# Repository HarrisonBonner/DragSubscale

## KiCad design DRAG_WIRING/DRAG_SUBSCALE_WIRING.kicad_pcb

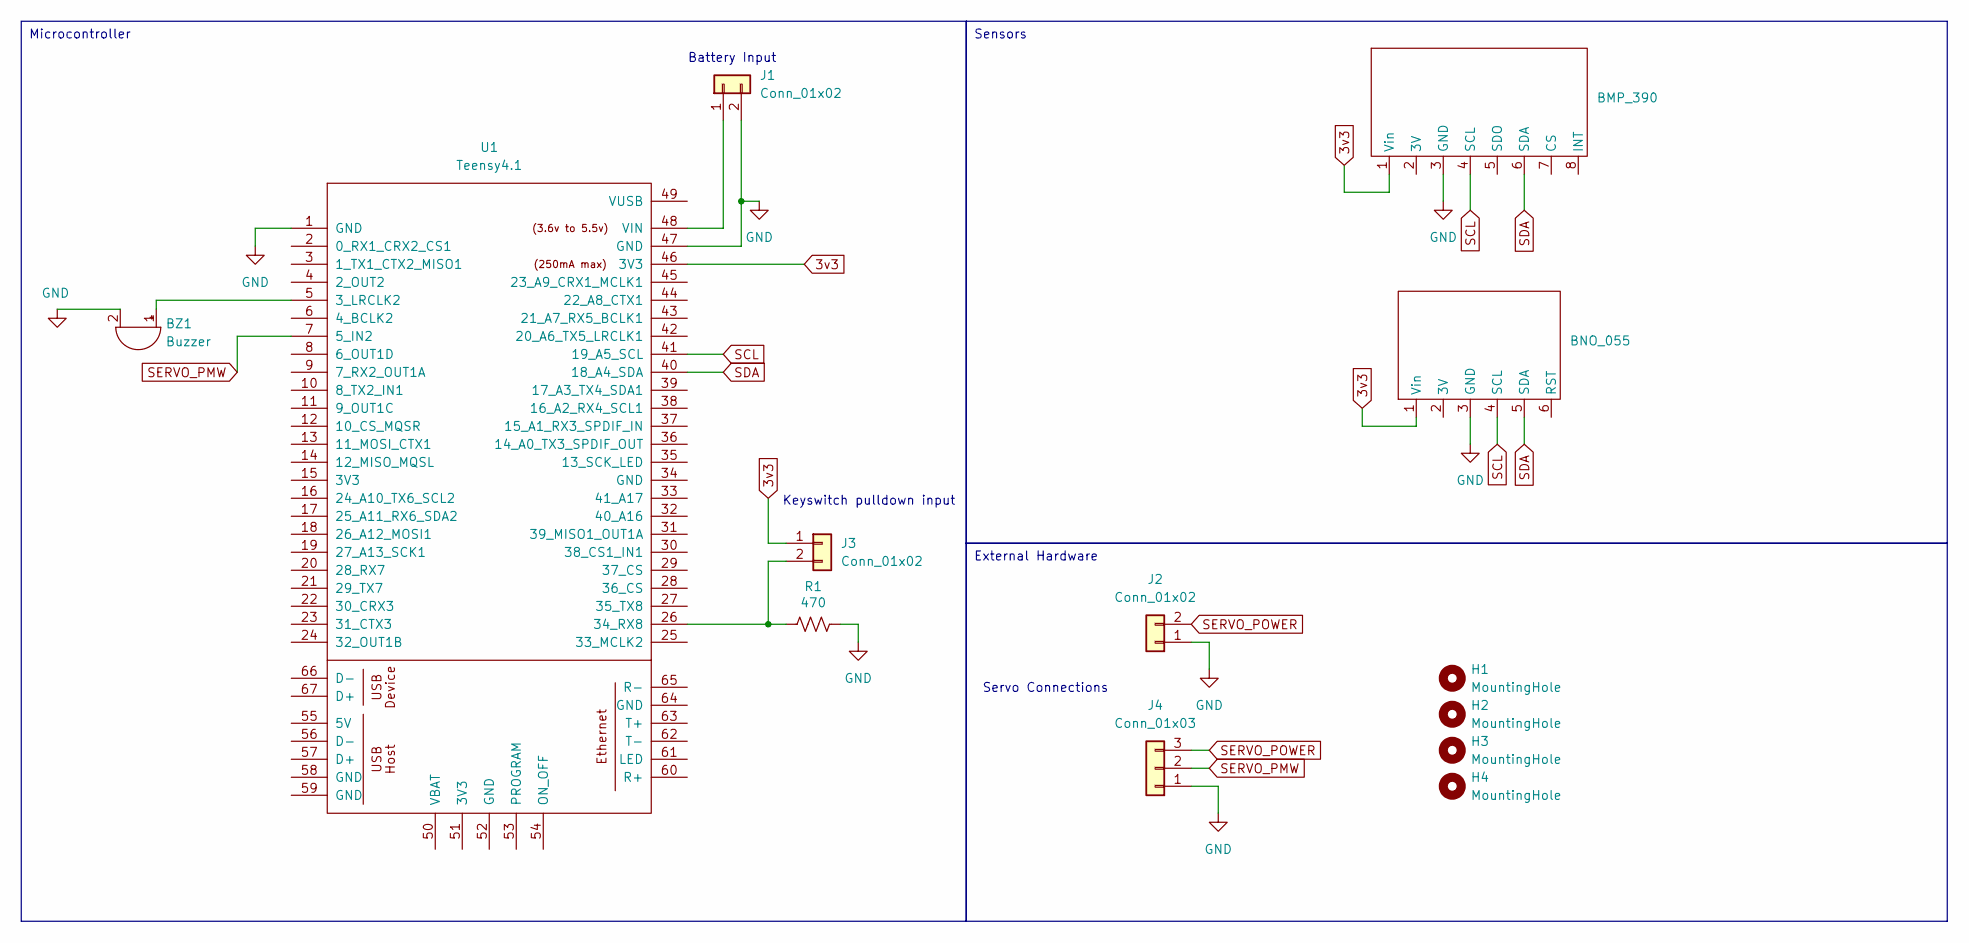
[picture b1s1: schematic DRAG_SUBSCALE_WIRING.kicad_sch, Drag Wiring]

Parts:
BMP_390: BMP390
BNO_055: BNO055Ada
BZ1: Buzzer; Buzzer_TDK_PS1240P02BT_D12.2mm_H6.5mm
H1, H2, H3, H4: MountingHole; MountingHole_3.2mm_M3_DIN965
J1, J2, J3: Conn_01x02; JST_XA_B02B-XASK-1_1x02_P2.50mm_Vertical
J4: Conn_01x03; JST_EH_B3B-EH-A_1x03_P2.50mm_Vertical
R1: 470; R_Axial_DIN0411_L9.9mm_D3.6mm_P15.24mm_Horizontal
U1: Teensy4.1; Teensy41

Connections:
3v3: BMP_390.1 (Vin), BNO_055.1 (Vin), J3.1, U1.46 (3V3)
GND: BMP_390.3 (GND), BNO_055.3 (GND), BZ1.2 (-), J1.2, J2.1, J4.1, R1.2, U1.1 (GND), U1.47 (GND)
unnamed: BZ1.1 (+), U1.5 (3_LRCLK2)
unnamed: J1.1, U1.48 (VIN)
unnamed: J3.2, R1.1, U1.26 (34_RX8)
SCL: BMP_390.4 (SCL), BNO_055.4 (SCL), U1.41 (19_A5_SCL)
SDA: BMP_390.6 (SDA), BNO_055.5 (SDA), U1.40 (18_A4_SDA)
SERVO_PMW: J4.2, U1.7 (5_IN2)
SERVO_POWER: J2.2, J4.3

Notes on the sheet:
Sensors
Microcontroller
External Hardware
Servo Connections
Keyswitch pulldown input
Battery Input

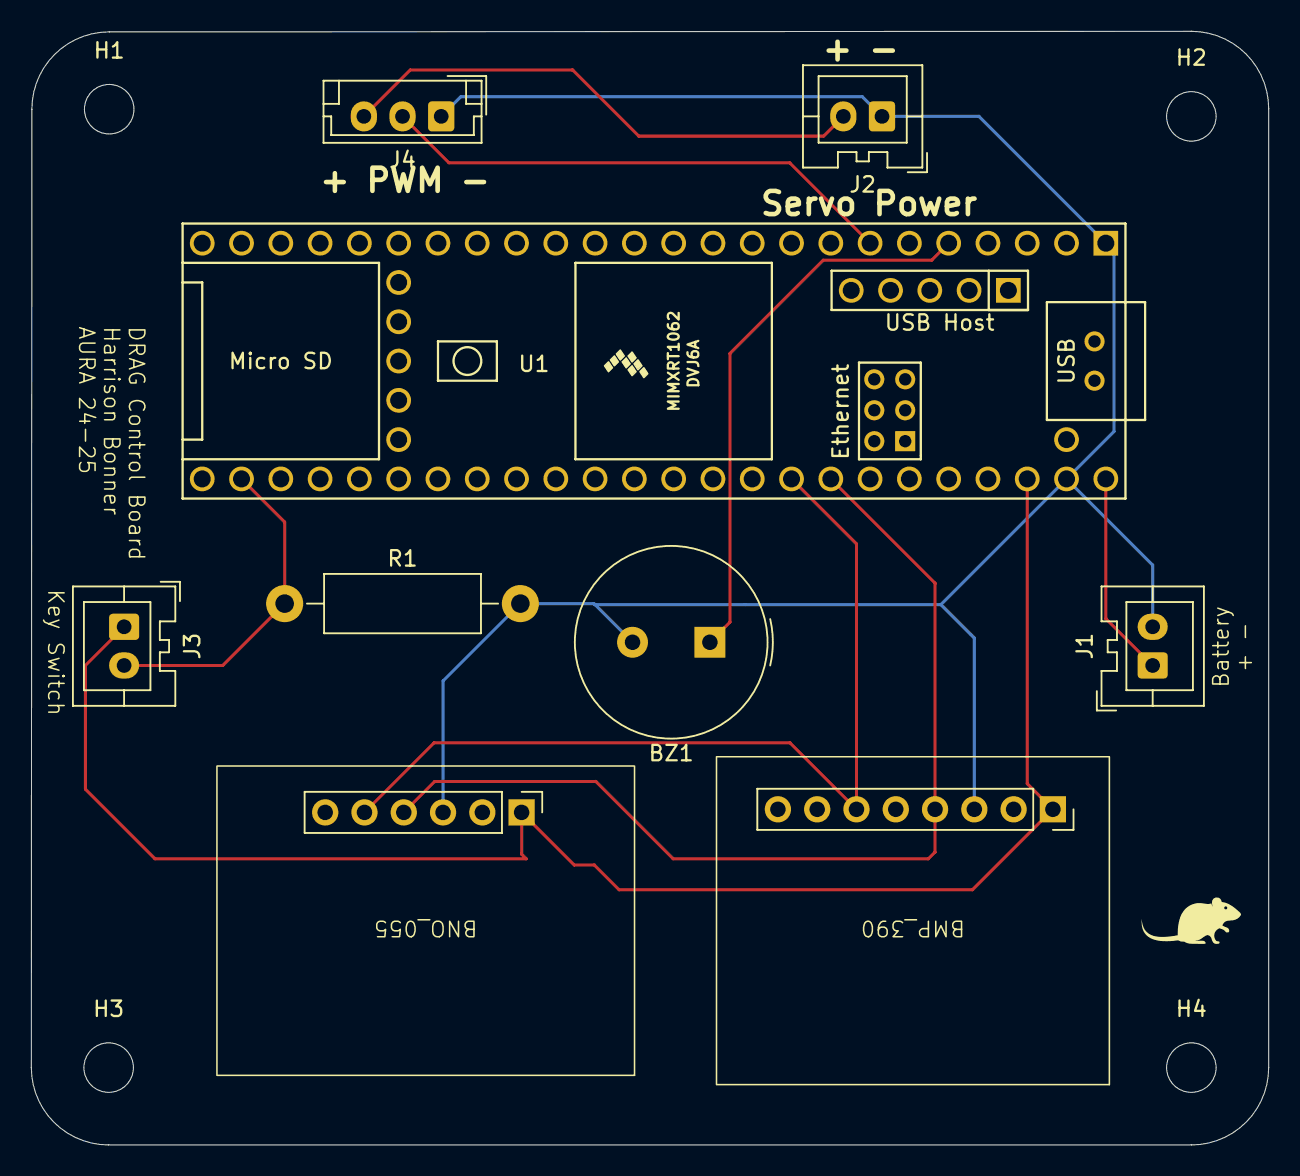
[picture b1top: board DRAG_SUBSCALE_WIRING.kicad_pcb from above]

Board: 2 copper layers, 80.0 x 72.0 mm, 13 parts (0 on the bottom side), 9 nets.

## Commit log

2024-09-25 Create DRAG_SUBSCALE_DATALOGGER.ino
    First commit of SD Logger for drag subscale
2024-09-28 Added schematics to wire subscale
2024-09-30 reformatted datalog still needs units to be added
2024-10-22 Added buzzer
2024-10-24 Added Key Switch
2024-10-24 Changed buzzer to be more pronounced pitch
2024-11-09 adding subscale flight data
2024-11-10 fixed space delimiter between time and altitude
2024-11-10 adding matlab script and excel sheet to parse and display data
2024-11-10 Updated graph display
2024-11-10 basic mov mean filter on linearAccel and Accel
2024-11-28 worked on pcb and adding 3d models
2024-11-28 set up enviroment for testing custom g range function
2024-12-29 updating to fullscale
2025-01-21 Updating wiring and pcb for servo
2025-01-28 working on servo support/Launch/Burnout detection
2025-01-29 Added launch/burnout detection, need to add apogee detection and ground calibration
2025-01-31 Fixed servo direction
2025-01-31 Added more to apogee preditction, adding extra datalog elements, decreased threshold counts
2025-02-05 testing apogee prediction and detections
2025-02-05 datalog working properly
2025-02-05 Changed to non conitnous servo
